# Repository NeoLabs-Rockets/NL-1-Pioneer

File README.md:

<div align="center">

# NeoLabs-Rockets NL-1 Pioneer

**Rocket systems by NeoLabs — The rocket to start it all**

---

[Compatible with NeoLabs-Rockets launch system](https://github.com/NeoLabs-Rockets/Launch-System) -
[Compatible with NeoLabs-Rockets launch platform](https://github.com/NeoLabs-Rockets/Launch-Platform)

---

The **NL-1 Pioneer** is the very first rocket developed under the NeoLabs-Rockets project. Designed as an affordable and modular entry point into model rocketry, it serves as the foundation for future NeoLabs rocket designs.

This version is intentionally simple and lightweight. It is currently **non-reusable** (except in special recovery situations), as it does not yet include a parachute or other dedicated recovery system. The focus is on providing an easy-to-build, reliable platform for learning, testing, and future upgrades.

The rocket is designed to be **modular**, **low-cost**, and **easy to extend** with future payloads or recovery systems. Most parts are **print-in-place**, minimizing assembly effort while keeping the design accessible for anyone with a standard 3D printer.

</div>

<div align="center">
  
# Compatible with the following motors

| Manufacturer | Motors |
|--------------|--------|
| Estes | 1/2A6-2, A8-3, B4-2, B6-4, B6-6, C5-3, C6-3, C6-5, C6-7 |
| Quest | A6-4, A8-3, B6-2, B6-4, C6-3, C6-5 |
| Klima | B2, B4, C6 |
| AeroTech (Q-Jet) | C12, C18, D10, D13, D20 *(some variants may be slightly longer than 70 mm)* |

</div>

# Print Settings

* **Material:** ABS is recommended for improved heat resistance and durability. PLA+ also works well for normal use.
* **Infill:** The lower, the better. **5%** is recommended to reduce weight while maintaining sufficient strength.
* **Orientation:** Print the model vertically for the best structural performance.
* **Supports:** Enable normal supports (Auto) with a **5° overhang angle**.

<div align="center">

</div>

---

<div align="center">

*Made with ❤️ by [Neo](https://github.com/neooriginal) · [NeoLabs Systems](https://github.com/NeoLabs-Systems)*

</div>

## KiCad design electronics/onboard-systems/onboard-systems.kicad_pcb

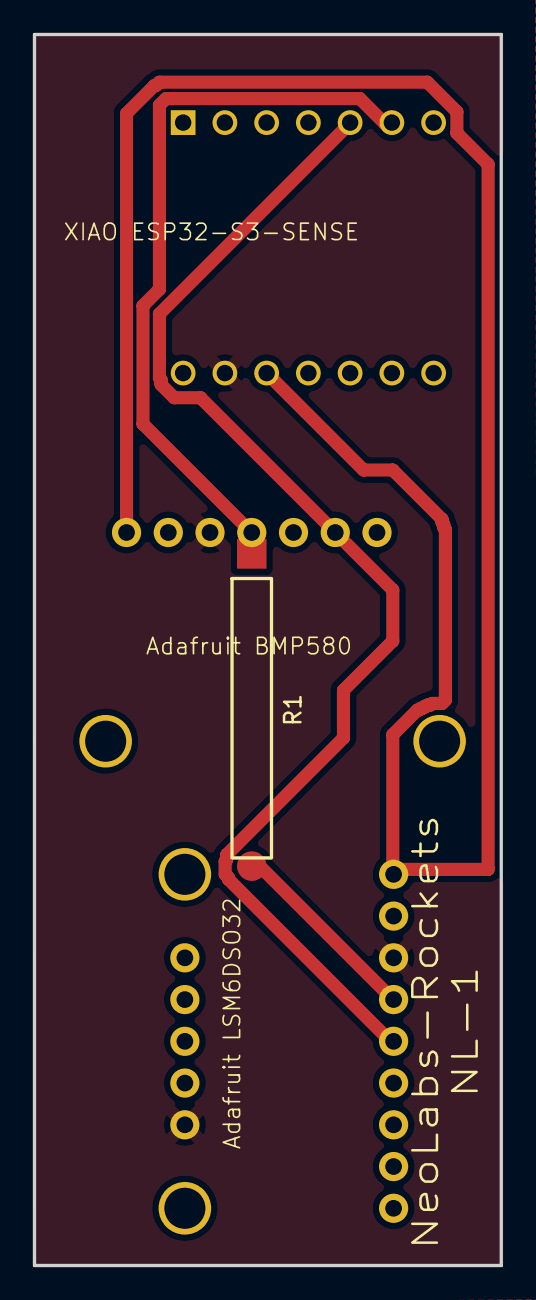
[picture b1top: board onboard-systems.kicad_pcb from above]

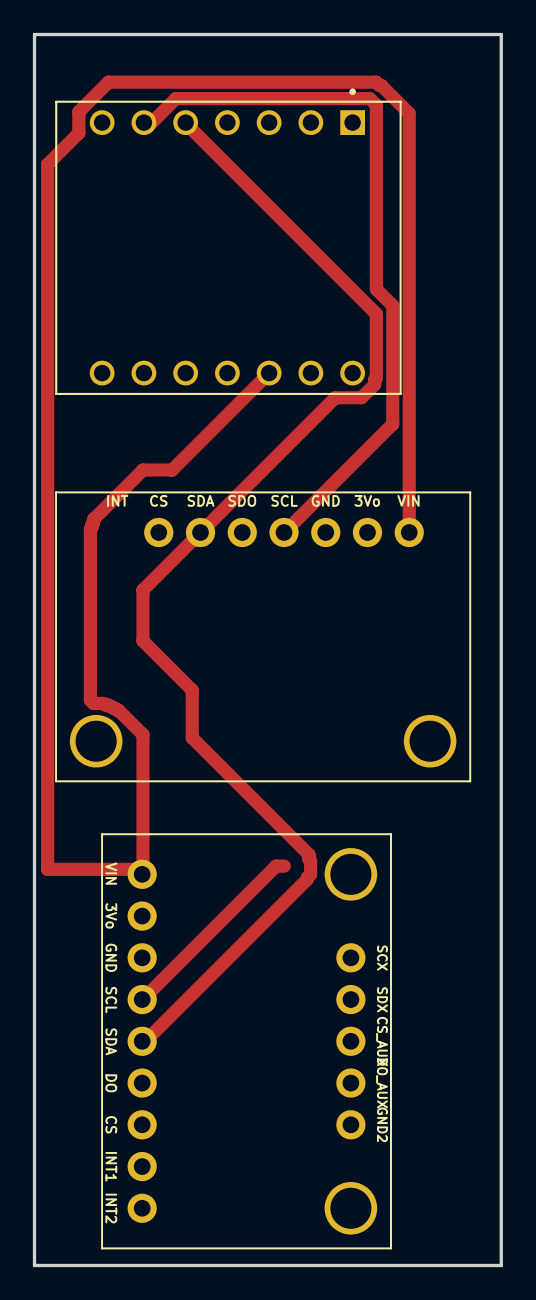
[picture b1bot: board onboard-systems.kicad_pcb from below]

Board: 2 copper layers, 28.4 x 74.9 mm, 4 parts (3 on the bottom side), 4 nets.

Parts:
R1: 0R; R_0R_THT_Custom
U1: XIAO_ESP32_S3; MODULE_XIAO_ESP32_S3
U2: Adafruit_BMP580; Adafruit_BMP580_Breakout
U3: Adafruit_LSM6DSO32; Adafruit_LSM6DSO32_Breakout

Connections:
GND: U1.13 (GND), U2.3 (GND), U3.3 (GND), U3.14 (GND2)
unnamed: U1.12 (3V3), U2.1 (VIN), U3.1 (VIN)
unnamed: U1.5 (D4/GPIO5), U2.6 (SDA), U3.5 (SDA)
unnamed: R1.1, U1.6 (D5/GPIO6), U2.4 (SCL), U3.4 (SCL)
